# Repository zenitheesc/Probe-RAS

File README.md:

<h1 align="center" style="color:white; background-color:black">Probe-RAS</h1>
<h4 align="center"> Telecommunication board for the Zenith's Stack architecture.</h4>

<p align="center">

</p>

<p align="center">
    <a href="#environment-and-tools">Environment and Tools</a> •
    <a href="#Z-Hub">Z-Hub</a> •
    <a href="#Block-Diagram">Block Diagram</a> •
    <a href="#Schematic">Schematic</a> • 
    <a href="#Board">Board</a>
</p>

## Environment and tools

This board was designed using KiCad 5.1.10.

## Block Diagram

## Z-Hub

This board contains a Stack Connector, with the 2021 Z-Hub pinout.

<table align = "center">
  <thead>
    <tr>
      <th colspan=2>   Z-Hub 2021   </th>
    </tr>
  </thead>
  <tbody>
    <tr>
      <td>GND</td>
      <td>GND</td>
    </tr>
    <tr>
      <td>GND</td>
      <td>GND</td>
    </tr>
    <tr>
      <td>BAT+</td>
      <td>BAT+</td>
    </tr>
    <tr>
      <td>SOl+</td>
      <td>SOl-</td>
    </tr>
    <tr>
      <td>5V</td>
      <td>5V</td>
    </tr>
    <tr>
      <td>3V3</td>
      <td>3V3</td>
    </tr>
    <tr>
      <td>MISO1</td>
      <td>MOSI1</td>
    </tr>
    <tr>
      <td>SCK1</td>
      <td>CAN_H</td>
    </tr>
    <tr>
      <td>SDA </td>
      <td>CAN_L</td>
    </tr>
    <tr>
      <td>SCL</td>
      <td>CE02</td>
    </tr>
    <tr>
      <td>CE11</td>
      <td>CE12</td>
    </tr>
    <tr>
      <td>SDA1</td>
      <td>SCL1</td>
    </tr>
    <tr>
      <td>SDA2</td>
      <td>SCL2</td>
    </tr>
    <tr>
      <td>TX1</td>
      <td>RX1</td>
    </tr>
    <tr>
      <td>TX2</td>
      <td>RX2</td>
    </tr>
    <tr>
      <td>DIG1</td>
      <td>DIG6</td>
    </tr>
    <tr>
      <td>ALRT1</td>
      <td>/CHRG</td>
    </tr>
    <tr>
      <td>PWM</td>
      <td>DIG8</td>
    </tr>
    <tr>
      <td>/FAULT</td>
      <td>DIG9</td>
    </tr>
    <tr>
      <td>DIG5</td>
      <td>DIG10</td>
    </tr>
  </tbody>
</table>

## Schematic

The design was separated in hierarchical sheets to accommodate all components in an orderly way.

The first page contains the STM32L476 with all its accompanying circuits; crystals, debugging LED, Boot solder jumper, decoupling capacitors and reset button. On the same page you find the stack connector along with a programming and debugging connector, as well as the I2C pull-ups for all I2C lines. 

The second page contains the basic peripherals, such as the CAN transceiver, the 128 Mb flash memory and the SD card.

The last page contains all the sensors implemented on this board. The I2C ones are divided in two lines, the first one being I2CA, which covers the MS5607 Barometer, the HDC-1080 Humidity sensor and the ZMOD4410 CO2 and air quality sensor. The second I2C line is I2CB, focused on the attitude of the probe, covering the MPU-6050 Accelerometer and the MMC5983 Magnetometer.
This page also contains the Thermistor Interfaces, connected to the STM32 via SPI, but note that these components only use the MISO connection of the SPI line.
The last component that this page contains is the MPX5071GP, which outputs pressure data via a 5V line, read via an ADC by the STM32.

## Board

---

<p align="center">

</p>
<p align = "center">
<a href="zenith.eesc@gmail.com">zenith.eesc@gmail.com</a>
</p>

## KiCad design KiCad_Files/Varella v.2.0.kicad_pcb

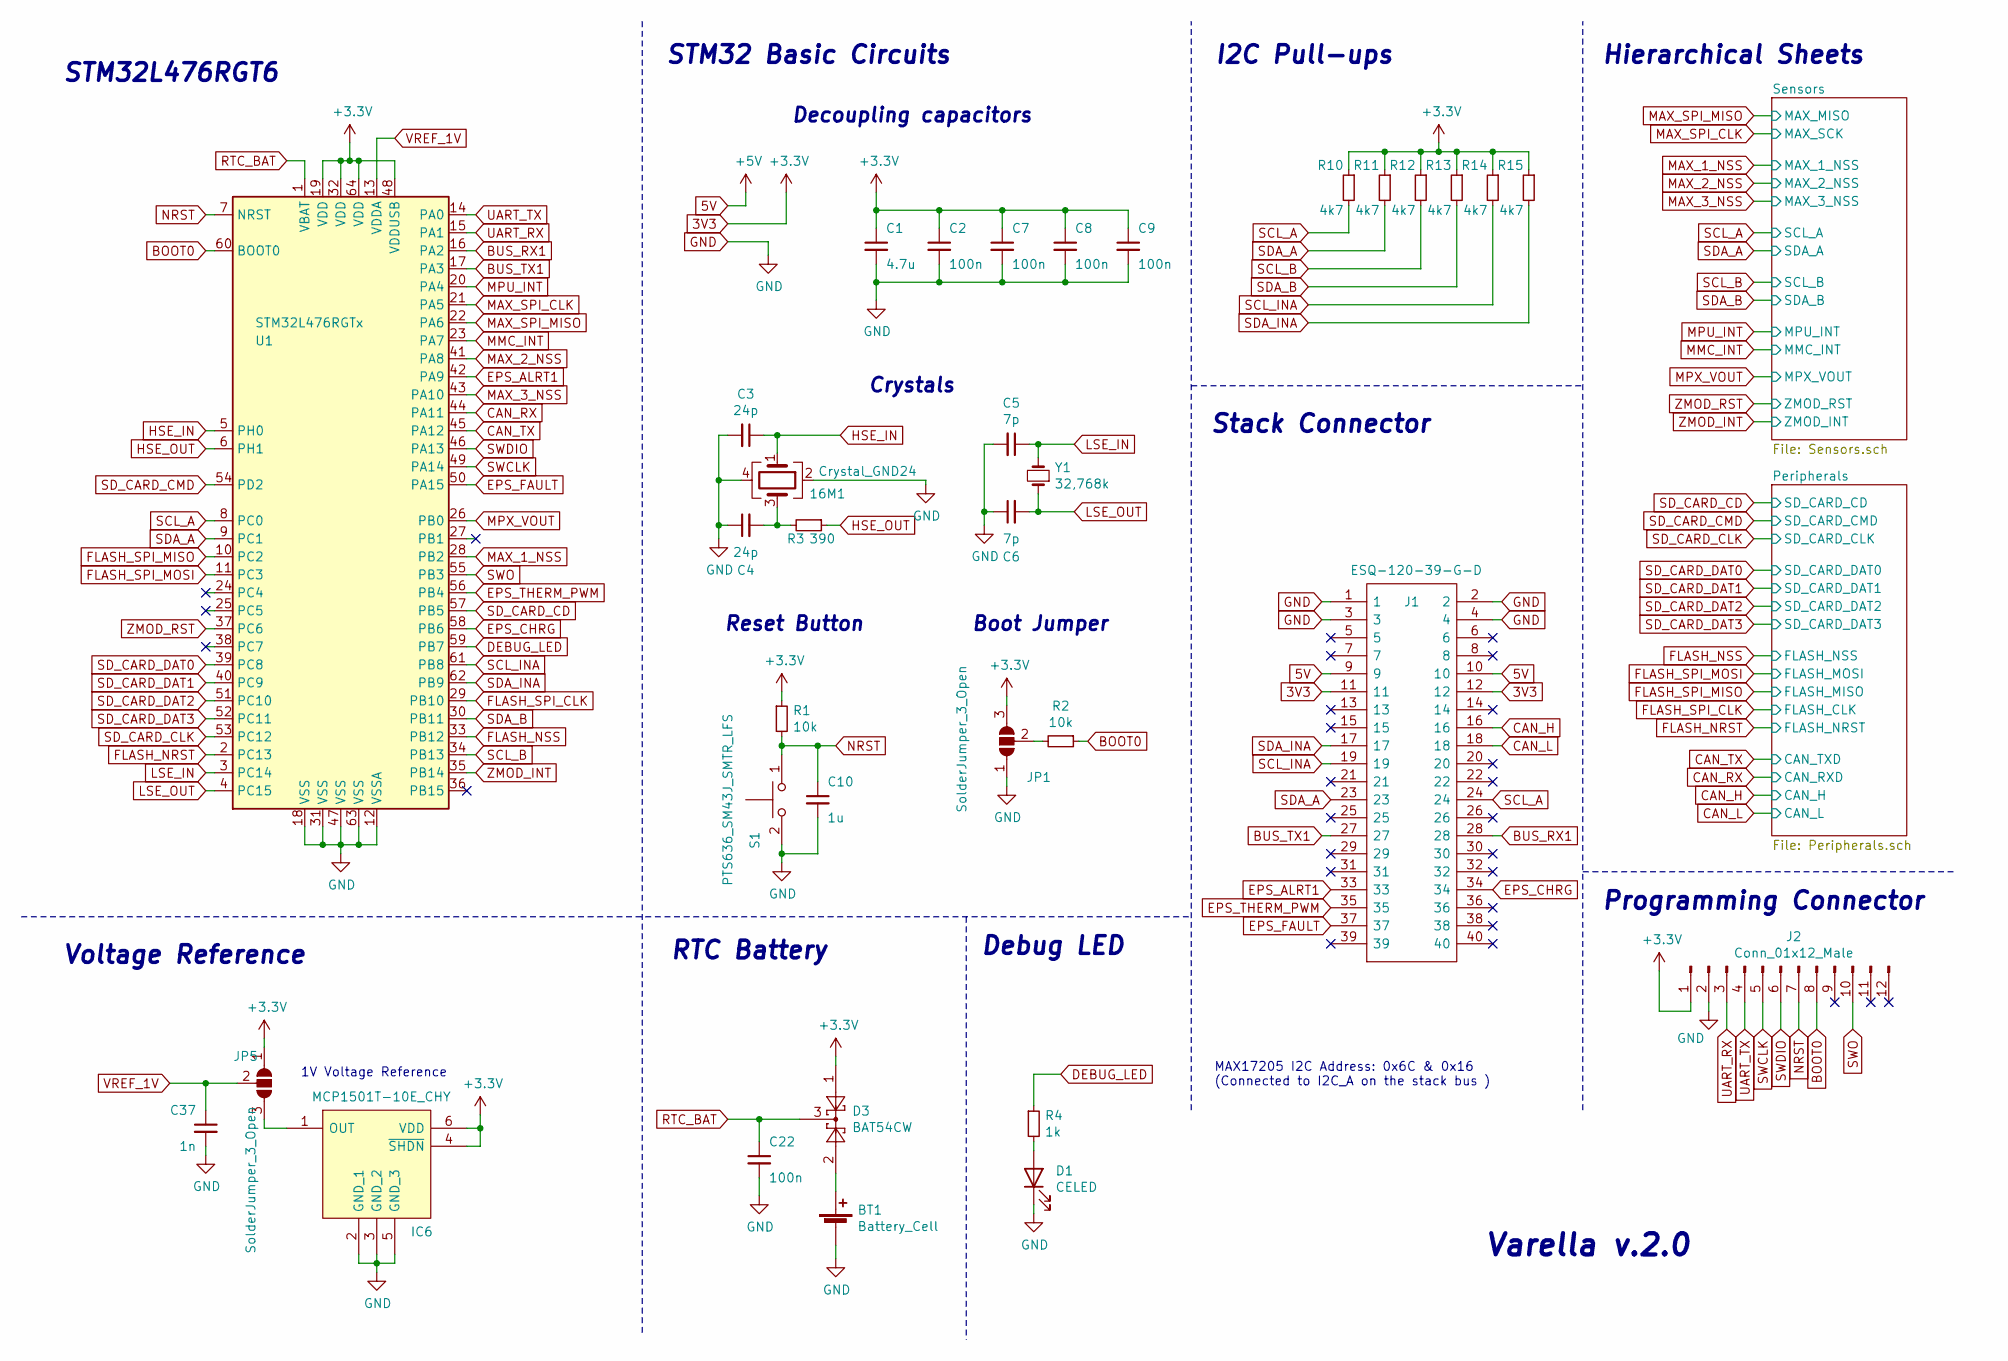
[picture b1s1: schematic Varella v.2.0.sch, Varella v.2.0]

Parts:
16M1: Crystal_GND24; Crystal_SMD_5032-4Pin_5.0x3.2mm_Hand_Soldering
BT1: Battery_Cell; 3030
C1: 4.7u; C_0805_2012Metric
C2, C7: 100n; C_0805_2012Metric
C3, C4: 24p; C_0805_2012Metric
C5, C6: 7p; C_0805_2012Metric
C8, C9, C22: 100n; C_0603_1608Metric
C10: 1u; C_0805_2012Metric
C37: 1n; C_0603_1608Metric
D1: CELED; LED_0805_2012Metric
D3: BAT54CW; SOT-323_SC-70
IC6: MCP1501T-10E_CHY; SOT95P280X145-6N; Mouser Part Number 579-MCP1501T-10E/CHY
J1: ESQ-120-39-G-D; ESQ-120-Y-X-D; Mouser Part Number 200-ESQ12039GD
J2: Conn_01x12_Male; 532611071
JP1, JP5: SolderJumper_3_Open; SolderJumper-3_P1.3mm_Open_RoundedPad1.0x1.5mm_NumberLabels
R1, R2: 10k; R_0805_2012Metric
R3: 390; R_0805_2012Metric
R4: 1k; R_0805_2012Metric
R10, R11, R12, R13, R14, R15: 4k7; R_0805_2012Metric
S1: PTS636_SM43J_SMTR_LFS; PTS636SM43JSMTRLFS; Mouser Part Number 611-PTS636SM43JSMTRL
U1: STM32L476RGTx; LQFP-64_10x10mm_P0.5mm
Y1: 32,768k; Crystal_SMD_3215-2Pin_3.2x1.5mm

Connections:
3V3: C1.1, C2.1, C7.1, C8.1, C9.1, D3.1, IC6.4 (~SHDN), IC6.6 (VDD), J1.11, J1.12, J2.1, JP1.3 (B), JP5.1 (A), R1.1, R10.1, R11.1, R12.1, R13.1, R14.1, R15.1, U1.19 (VDD), U1.32 (VDD), U1.48 (VDDUSB), U1.64 (VDD); also elsewhere on the board
5V: J1.9, J1.10; also elsewhere on the board
BOOT0: J2.8, R2.1, U1.60 (BOOT0)
BUS_RX1: J1.28, U1.16 (PA2)
BUS_TX1: J1.27, U1.17 (PA3)
CAN_H: J1.16; also elsewhere on the board
CAN_L: J1.18; also elsewhere on the board
CAN_RX: U1.44 (PA11); also elsewhere on the board
CAN_TX: U1.45 (PA12); also elsewhere on the board
DEBUG_LED: R4.1, U1.59 (PB7)
EPS_ALRT1: J1.33, U1.42 (PA9)
EPS_CHRG: J1.34, U1.58 (PB6)
EPS_FAULT: J1.37, U1.50 (PA15)
EPS_THERM_PWM: J1.35, U1.56 (PB4)
FLASH_NRST: U1.2 (PC13); also elsewhere on the board
FLASH_NSS: U1.33 (PB12); also elsewhere on the board
FLASH_SPI_CLK: U1.29 (PB10); also elsewhere on the board
FLASH_SPI_MISO: U1.10 (PC2); also elsewhere on the board
FLASH_SPI_MOSI: U1.11 (PC3); also elsewhere on the board
GND: 16M1.2, 16M1.4, BT1.2 (-), C1.2, C2.2, C3.2, C4.1, C5.2, C6.1, C7.2, C8.2, C9.2, C10.2, C22.2, C37.2, D1.1 (K), IC6.2 (GND_1), IC6.3 (GND_2), IC6.5 (GND_3), J1.1, J1.2, J1.3, J1.4, J2.2, JP1.1 (A), S1.2, U1.12 (VSSA), U1.18 (VSS), U1.31 (VSS), U1.47 (VSS), U1.63 (VSS); also elsewhere on the board
HSE_IN: 16M1.1, C3.1, U1.5 (PH0)
HSE_OUT: R3.1, U1.6 (PH1)
LSE_IN: C5.1, U1.3 (PC14), Y1.2
LSE_OUT: C6.2, U1.4 (PC15), Y1.1
MAX_1_NSS: U1.28 (PB2); also elsewhere on the board
MAX_2_NSS: U1.41 (PA8); also elsewhere on the board
MAX_3_NSS: U1.43 (PA10); also elsewhere on the board
MAX_SPI_CLK: U1.21 (PA5); also elsewhere on the board
MAX_SPI_MISO: U1.22 (PA6); also elsewhere on the board
MMC_INT: U1.23 (PA7); also elsewhere on the board
MPU_INT: U1.20 (PA4); also elsewhere on the board
MPX_VOUT: U1.26 (PB0); also elsewhere on the board
NRST: C10.1, J2.7, R1.2, S1.1, U1.7 (NRST)
unnamed: 16M1.3, C4.2, R3.2
unnamed: BT1.1 (+), D3.2
unnamed: D1.2 (A), R4.2
unnamed: IC6.1 (OUT), JP5.3 (B)
unnamed: JP1.2 (C), R2.2
RTC_BAT: C22.1, D3.3, U1.1 (VBAT)
SCL_A: J1.24, R10.2, U1.8 (PC0); also elsewhere on the board
SCL_B: R12.2, U1.34 (PB13); also elsewhere on the board
SCL_INA: J1.19, R14.2, U1.61 (PB8)
SDA_A: J1.23, R11.2, U1.9 (PC1); also elsewhere on the board
SDA_B: R13.2, U1.30 (PB11); also elsewhere on the board
SDA_INA: J1.17, R15.2, U1.62 (PB9)
SD_CARD_CD: U1.57 (PB5); also elsewhere on the board
SD_CARD_CLK: U1.53 (PC12); also elsewhere on the board
SD_CARD_CMD: U1.54 (PD2); also elsewhere on the board
SD_CARD_DAT0: U1.39 (PC8); also elsewhere on the board
SD_CARD_DAT1: U1.40 (PC9); also elsewhere on the board
SD_CARD_DAT2: U1.51 (PC10); also elsewhere on the board
SD_CARD_DAT3: U1.52 (PC11); also elsewhere on the board
SWCLK: J2.5, U1.49 (PA14)
SWDIO: J2.6, U1.46 (PA13)
SWO: J2.10, U1.55 (PB3)
UART_RX: J2.3, U1.15 (PA1)
UART_TX: J2.4, U1.14 (PA0)
VREF_1V: C37.1, JP5.2 (C), U1.13 (VDDA)
ZMOD_INT: U1.35 (PB14); also elsewhere on the board
ZMOD_RST: U1.37 (PC6); also elsewhere on the board

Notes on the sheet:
Programming Connector
Stack Connector
Hierarchical Sheets
Varella v.2.0
STM32L476RGT6
I2C Pull-ups
MAX17205 I2C Address: 0x6C & 0x16 (Connected to I2C_A on the stack bus )
1V Voltage Reference
Voltage Reference
RTC Battery
Debug LED
STM32 Basic Circuits
Crystals
Decoupling capacitors
Reset Button
Boot Jumper

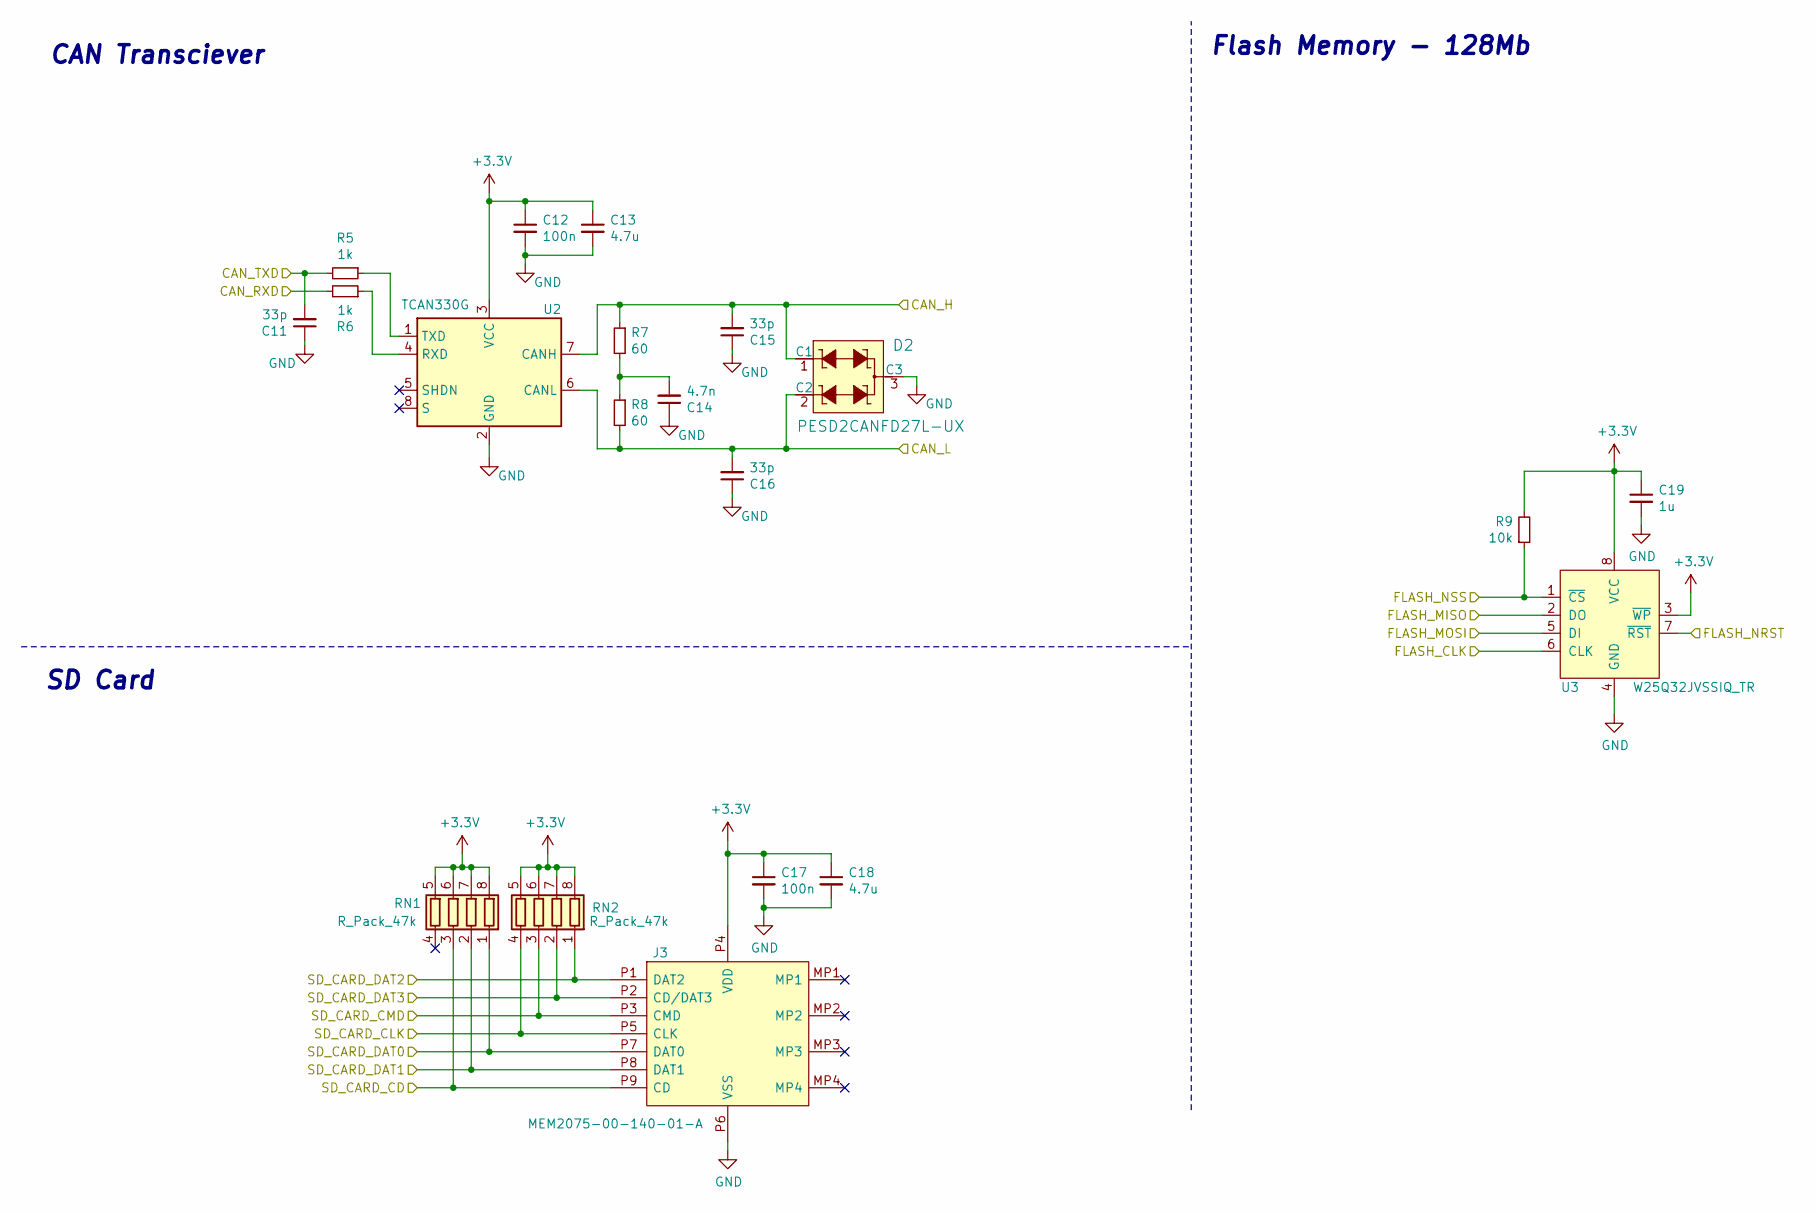
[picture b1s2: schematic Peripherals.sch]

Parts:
C11, C15, C16: 33p; C_0805_2012Metric
C12, C17: 100n; C_0805_2012Metric
C13, C18: 4.7u; C_0805_2012Metric
C14: 4.7n; C_0805_2012Metric
C19: 1u; C_0805_2012Metric
D2: PESD2CANFD27L-UX; SOT-23-3; MPN PESD2CAN,215; Digi-Key_PN 1727-3891-1-ND
J3: MEM2075-00-140-01-A; MEM20750014001A; Mouser Part Number 640-MEM20750014001A
R5, R6: 1k; R_0805_2012Metric
R7, R8: 60; R_0805_2012Metric
R9: 10k; R_0805_2012Metric
RN1, RN2: R_Pack_47k; YC164JR07220RL
U2: TCAN330G; SOIC-8_3.9x4.9mm_P1.27mm
U3: W25Q32JVSSIQ_TR; SOIC-8_W5.6mm; MPN W25Q32JVSSIQ TR; Digi-Key_PN W25Q32JVSSIQCT-ND

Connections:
3V3: C12.1, C13.1, C17.1, C18.1, C19.1, J3.P4 (VDD), R9.2, RN1.5 (R4.2), RN1.6 (R3.2), RN1.7 (R2.2), RN1.8 (R1.2), RN2.5 (R4.2), RN2.6 (R3.2), RN2.7 (R2.2), RN2.8 (R1.2), U2.3 (VCC), U3.3 (~WP), U3.8 (VCC); also elsewhere on the board
CAN_H: C15.2, D2.1 (C1), R7.1, U2.7 (CANH); also elsewhere on the board
CAN_L: C16.2, D2.2 (C2), R8.2, U2.6 (CANL); also elsewhere on the board
CAN_RX: R6.2; also elsewhere on the board
CAN_TX: C11.2, R5.2; also elsewhere on the board
FLASH_NRST: U3.7 (~RST); also elsewhere on the board
FLASH_NSS: R9.1, U3.1 (~CS); also elsewhere on the board
FLASH_SPI_CLK: U3.6 (CLK); also elsewhere on the board
FLASH_SPI_MISO: U3.2 (DO); also elsewhere on the board
FLASH_SPI_MOSI: U3.5 (DI); also elsewhere on the board
GND: C11.1, C12.2, C13.2, C14.1, C15.1, C16.1, C17.2, C18.2, C19.2, D2.3 (C3), J3.P6 (VSS), U2.2 (GND), U3.4 (GND); also elsewhere on the board
unnamed: C14.2, R7.2, R8.1
unnamed: R5.1, U2.1 (TXD)
unnamed: R6.1, U2.4 (RXD)
SD_CARD_CD: J3.P9 (CD), RN1.3 (R3.1); also elsewhere on the board
SD_CARD_CLK: J3.P5 (CLK), RN2.4 (R4.1); also elsewhere on the board
SD_CARD_CMD: J3.P3 (CMD), RN2.3 (R3.1); also elsewhere on the board
SD_CARD_DAT0: J3.P7 (DAT0), RN1.1 (R1.1); also elsewhere on the board
SD_CARD_DAT1: J3.P8 (DAT1), RN1.2 (R2.1); also elsewhere on the board
SD_CARD_DAT2: J3.P1 (DAT2), RN2.1 (R1.1); also elsewhere on the board
SD_CARD_DAT3: J3.P2 (CD/DAT3), RN2.2 (R2.1); also elsewhere on the board

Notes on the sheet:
CAN Transciever
SD Card
Flash Memory - 128Mb

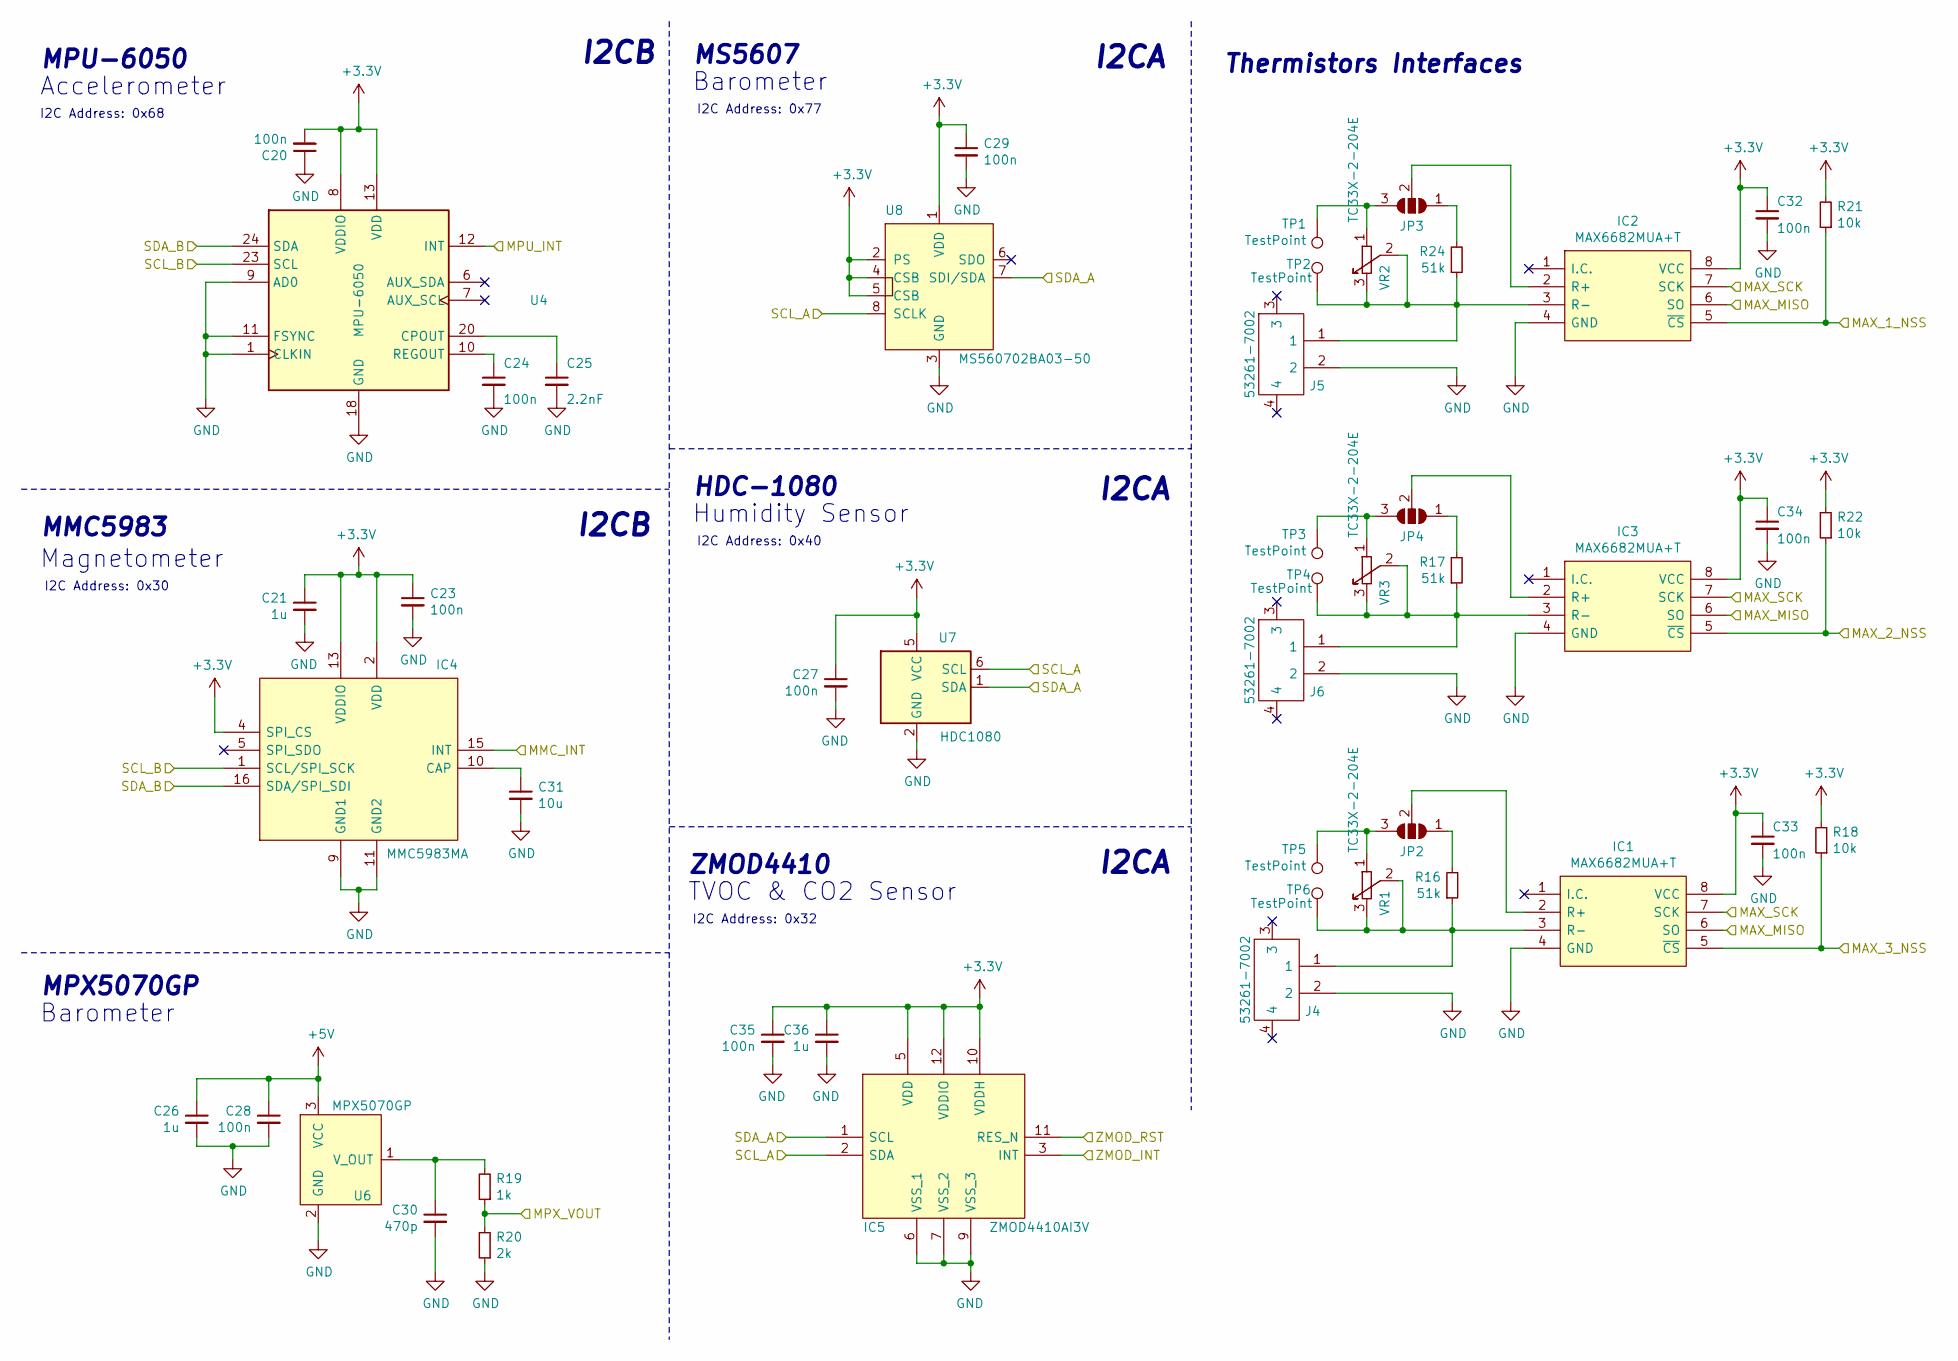
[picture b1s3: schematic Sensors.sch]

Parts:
C20, C23, C24, C27, C28, C29, C32, C33, C34, C35: 100n; C_0805_2012Metric
C21, C26, C36: 1u; C_0805_2012Metric
C25: 2.2nF; C_0805_2012Metric
C30: 470p; C_0805_2012Metric
C31: 10u; C_0805_2012Metric
IC1, IC2, IC3: MAX6682MUA+T; SOP65P490X110-8N; Mouser Part Number 700-MAX6682MUAT
IC4: MMC5983MA; Mouser Part Number 438-MMC5983MA
IC5: ZMOD4410AI3V; Mouser Part Number 972-ZMOD4410AI3V
J4, J5, J6: 53261-7002; 532617002; Mouser Part Number 538-53261-7002
JP2, JP3, JP4: SolderJumper_3_Open; SolderJumper-3_P1.3mm_Open_RoundedPad1.0x1.5mm_NumberLabels
R16, R17, R24: 51k; R_0805_2012Metric
R18, R21, R22: 10k; R_0805_2012Metric
R19: 1k; R_0805_2012Metric
R20: 2k; R_0805_2012Metric
TP1, TP2, TP3, TP4, TP5, TP6: TestPoint; TestPoint_Pad_D2.0mm
U4: MPU-6050; InvenSense_QFN-24_4x4mm_P0.5mm
U6: MPX5070GP
U7: HDC1080; Texas_PWSON-N6
U8: MS560702BA03-50; SMD-8_5x3mm; MPN MS560702BA03-50; Digi-Key_PN 223-1198-1-ND
VR1, VR2, VR3: TC33X-2-204E; TC33X-2_1; Mouser Part Number 652-TC33X-2-204E

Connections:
3V3: C20.2, C21.1, C23.1, C27.1, C29.1, C32.1, C33.1, C34.1, C35.1, C36.1, IC1.8 (VCC), IC2.8 (VCC), IC3.8 (VCC), IC4.2 (VDD), IC4.4 (SPI_CS), IC4.13 (VDDIO), IC5.5 (VDD), IC5.10 (VDDH), IC5.12 (VDDIO), R18.2, R21.2, R22.2, U4.8 (VDDIO), U4.13 (VDD), U7.5 (VCC), U8.1 (VDD), U8.2 (PS), U8.4 (CSB), U8.5 (CSB); also elsewhere on the board
5V: C26.1, C28.1, U6.3 (VCC); also elsewhere on the board
GND: C20.1, C21.2, C23.2, C24.2, C25.2, C26.2, C27.2, C28.2, C29.2, C30.2, C31.2, C32.2, C33.2, C34.2, C35.2, C36.2, IC1.4 (GND), IC2.4 (GND), IC3.4 (GND), IC4.9 (GND1), IC4.11 (GND2), IC5.6 (VSS_1), IC5.7 (VSS_2), IC5.9 (VSS_3), J4.2, J5.2, J6.2, R20.1, U4.1 (CLKIN), U4.9 (AD0), U4.11 (FSYNC), U4.18 (GND), U6.2 (GND), U7.2 (GND), U8.3 (GND); also elsewhere on the board
MAX_1_NSS: IC2.5 (~CS), R21.1; also elsewhere on the board
MAX_2_NSS: IC3.5 (~CS), R22.1; also elsewhere on the board
MAX_3_NSS: IC1.5 (~CS), R18.1; also elsewhere on the board
MAX_SPI_CLK: IC1.7 (SCK), IC2.7 (SCK), IC3.7 (SCK); also elsewhere on the board
MAX_SPI_MISO: IC1.6 (SO), IC2.6 (SO), IC3.6 (SO); also elsewhere on the board
MMC_INT: IC4.15 (INT); also elsewhere on the board
MPU_INT: U4.12 (INT); also elsewhere on the board
MPX_VOUT: R19.1, R20.2; also elsewhere on the board
unnamed: C24.1, U4.10 (REGOUT)
unnamed: C25.1, U4.20 (CPOUT)
unnamed: C30.1, R19.2, U6.1 (V_OUT)
unnamed: C31.1, IC4.10 (CAP)
unnamed: IC1.2 (R+), JP2.2 (C)
unnamed: IC1.3 (R-), J4.1, R16.1, TP6.1, VR1.2, VR1.3
unnamed: IC2.2 (R+), JP3.2 (C)
unnamed: IC2.3 (R-), J5.1, R24.1, TP2.1, VR2.2, VR2.3
unnamed: IC3.2 (R+), JP4.2 (C)
unnamed: IC3.3 (R-), J6.1, R17.1, TP4.1, VR3.2, VR3.3
unnamed: JP2.1 (A), R16.2
unnamed: JP2.3 (B), TP5.1, VR1.1
unnamed: JP3.1 (A), R24.2
unnamed: JP3.3 (B), TP1.1, VR2.1
unnamed: JP4.1 (A), R17.2
unnamed: JP4.3 (B), TP3.1, VR3.1
SCL_A: IC5.2 (SDA), U7.6 (SCL), U8.8 (SCLK); also elsewhere on the board
SCL_B: IC4.1 (SCL/SPI_SCK), U4.23 (SCL); also elsewhere on the board
SDA_A: IC5.1 (SCL), U7.1 (SDA), U8.7 (SDI/SDA); also elsewhere on the board
SDA_B: IC4.16 (SDA/SPI_SDI), U4.24 (SDA); also elsewhere on the board
ZMOD_INT: IC5.3 (INT); also elsewhere on the board
ZMOD_RST: IC5.11 (RES_N); also elsewhere on the board

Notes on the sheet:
Thermistors Interfaces
MPU-6050
MS5607
MMC5983
HDC-1080
Humidity Sensor
Magnetometer
Accelerometer
Barometer
MPX5070GP
I2C Address: 0x77
I2C Address: 0x40
I2C Address: 0x68
I2C Address: 0x30
ZMOD4410
TVOC & CO2 Sensor
I2C Address: 0x32
I2CA
I2CB

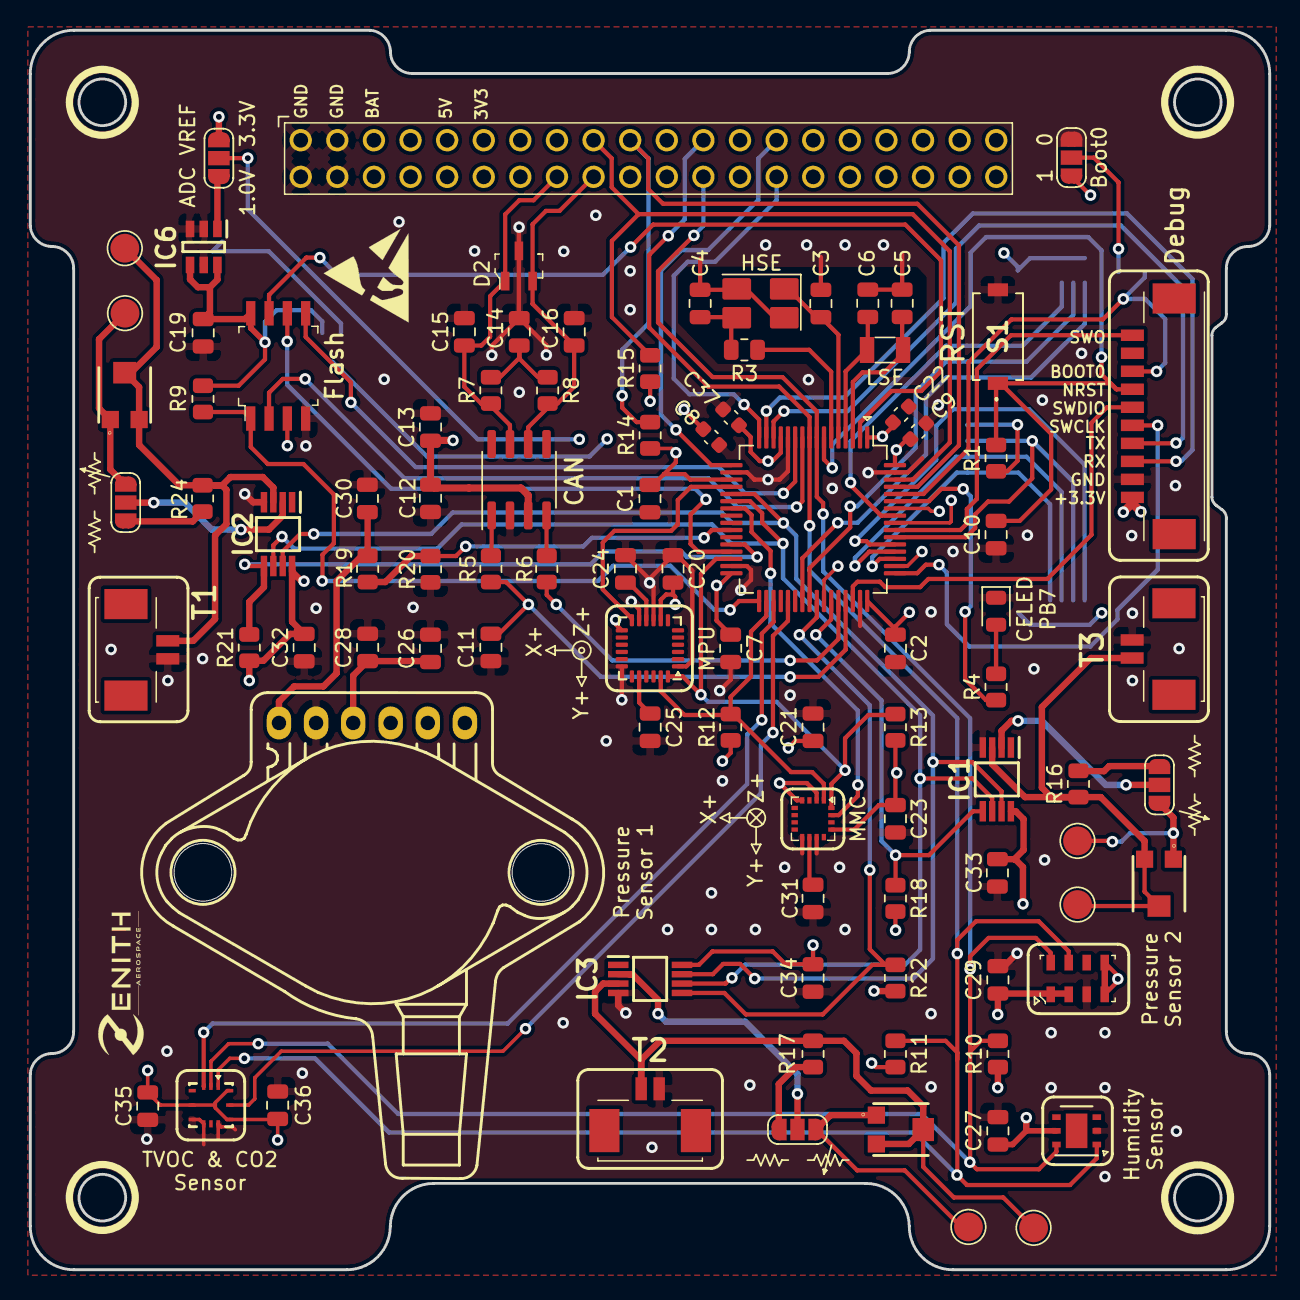
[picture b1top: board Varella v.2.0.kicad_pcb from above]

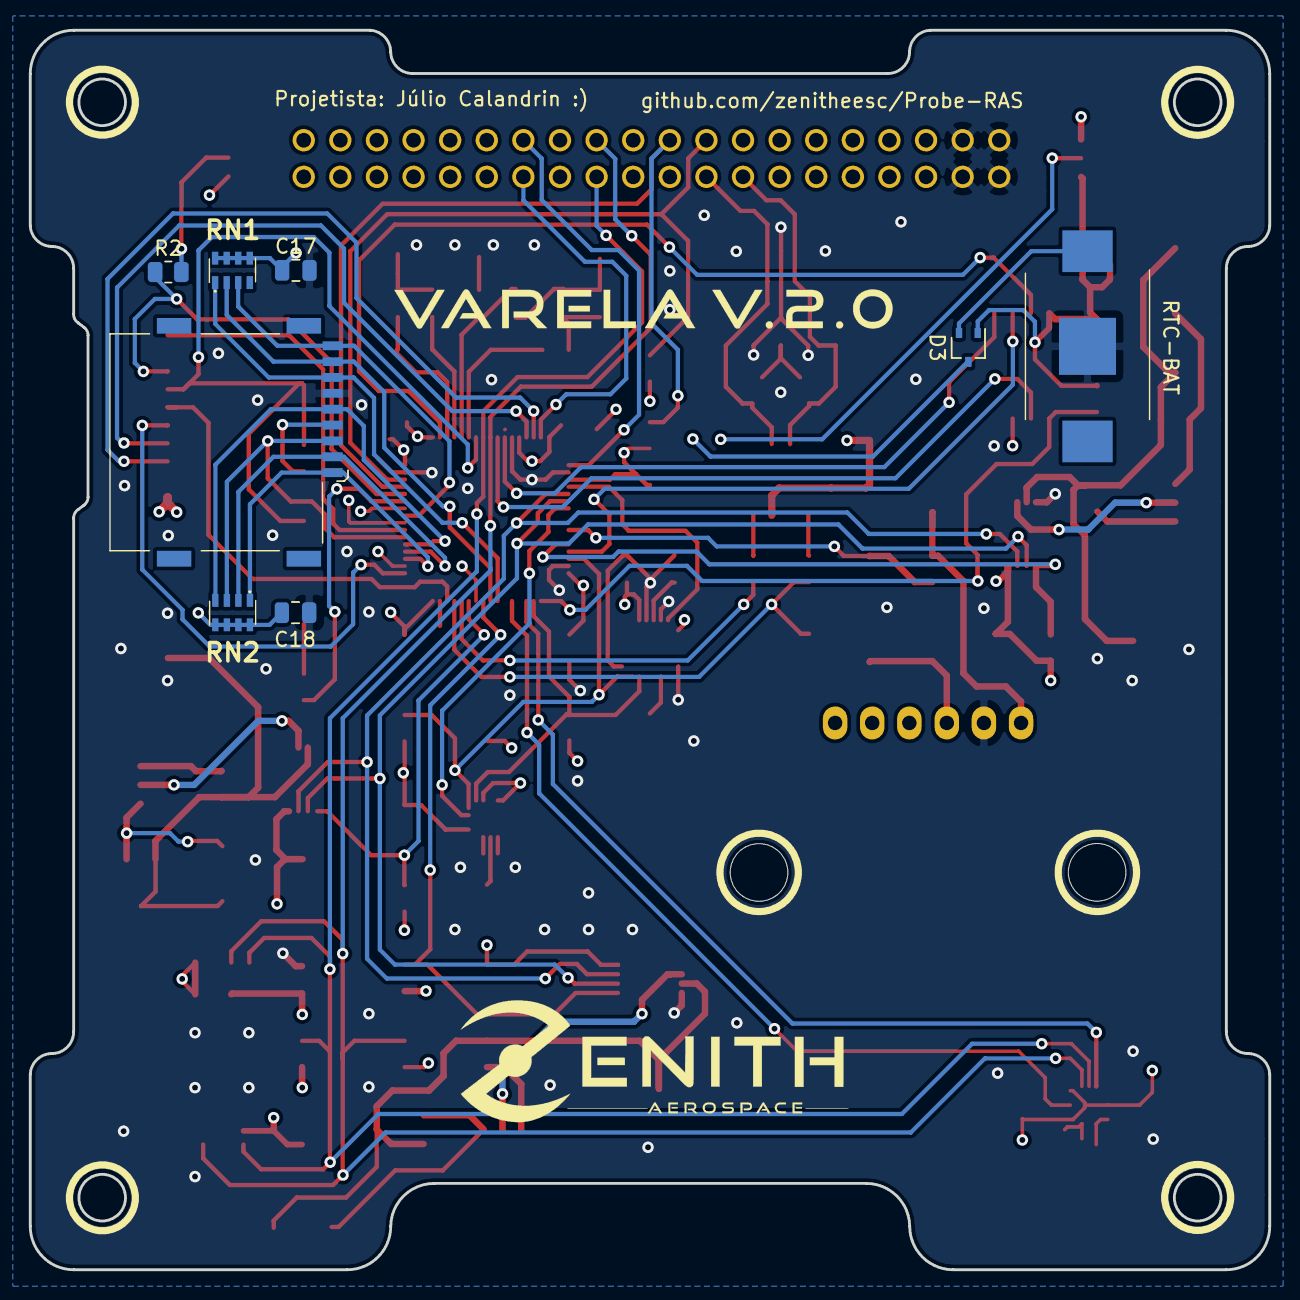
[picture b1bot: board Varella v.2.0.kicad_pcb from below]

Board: 4 copper layers, 86.0 x 86.0 mm, 102 parts (8 on the bottom side), 79 nets.

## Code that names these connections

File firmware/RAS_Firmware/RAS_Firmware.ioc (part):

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Mcu.Name=STM32L476R(C-E-G)Tx
Mcu.Package=LQFP64
Mcu.UserName=STM32L476RGTx
PA10.Mode=Asynchronous
PA10.Signal=USART1_RX
PA11.Mode=CAN_Activate
PA11.Signal=CAN1_RX
PA12.Mode=CAN_Activate
PA12.Signal=CAN1_TX
PA13\ (JTMS-SWDIO).Mode=Serial_Wire
PA13\ (JTMS-SWDIO).Signal=SYS_JTMS-SWDIO
PA14\ (JTCK-SWCLK).Mode=Serial_Wire
PA14\ (JTCK-SWCLK).Signal=SYS_JTCK-SWCLK
PA5.Mode=Full_Duplex_Master
PA5.Signal=SPI1_SCK
PA6.Mode=Full_Duplex_Master
PA6.Signal=SPI1_MISO
PA7.Mode=Full_Duplex_Master
PA7.Signal=SPI1_MOSI
PA9.Mode=Asynchronous
PA9.Signal=USART1_TX
PB5.Signal=GPIO_Input
PB6.Mode=I2C
PB6.Signal=I2C1_SCL
PB7.Mode=I2C
PB7.Signal=I2C1_SDA
PC10.Mode=SD_4_bits_Wide_bus
PC10.Signal=SDMMC1_D2
PC11.Mode=SD_4_bits_Wide_bus
PC11.Signal=SDMMC1_D3
PC12.Mode=SD_4_bits_Wide_bus
PC12.Signal=SDMMC1_CK
PC14-OSC32_IN\ (PC14).Mode=LSE-External-Oscillator
PC14-OSC32_IN\ (PC14).Signal=RCC_OSC32_IN
PC15-OSC32_OUT\ (PC15).Mode=LSE-External-Oscillator
PC15-OSC32_OUT\ (PC15).Signal=RCC_OSC32_OUT
PC8.Mode=SD_4_bits_Wide_bus
PC8.Signal=SDMMC1_D0
PC9.Mode=SD_4_bits_Wide_bus
PC9.Signal=SDMMC1_D1
PD2.Mode=SD_4_bits_Wide_bus
PD2.Signal=SDMMC1_CMD
PH0-OSC_IN\ (PH0).Mode=HSE-External-Oscillator
PH0-OSC_IN\ (PH0).Signal=RCC_OSC_IN
PH1-OSC_OUT\ (PH1).Mode=HSE-External-Oscillator
PH1-OSC_OUT\ (PH1).Signal=RCC_OSC_OUT
RCC.HSE_VALUE=8000000
RCC.SYSCLKFreq_VALUE=80000000
RCC.SYSCLKSource=RCC_SYSCLKSOURCE_PLLCLK
board=custom

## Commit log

2022-01-19 Add Board
2022-01-19 Add Block Diagram
2022-01-20 Add shapes3D folder
    Now all 3D models for the components are stored in a single folder, thanks to the Archive Plugin from https://github.com/MitjaNemec/Kicad_action_plugins.git
2022-01-20 Revert "Add shapes3D folder"
    This reverts commit 1c3042b7a1c052b8553a455bf3bd885d3494e48a.
2022-01-20 Add shapes3D folder again
    Something went wrong on the last commit. The hierarchical sheets had been corrupted after the archiving process, so I reverted the commit and did the procedure again. Everything appears to be working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
2022-01-20 Revert "Delete archive_project.log"
    This reverts commit 61f9e4587e3aeb6e86bf636a17929865b062fe7a.
2022-01-20 Revert "Add shapes3D folder again"
    This reverts commit 7987a310af828f940c17547aa6162ac2ebe2b018.
2022-01-20 Archive project
2022-01-20 Update Archive
2022-01-20 Archive Schematic
2022-01-26 README: Delete duplicated header
2022-01-27 Add Traces to Stack Connector
    Connects the Interrupts and PWM pins that come from the EPS boards through the Stack Connector to Varella's STM32.
2022-01-27 Add BOM and update image of the first page
2022-01-28 Gerado projeto da CubeIDE
2022-02-03 Correct diagram component name
    MAX6682 replaced the MAX31856 during development, but the diagram was never updated.
2022-02-05 Update RTC Battery Silk Screen name
2022-02-09 Add 1,024 V voltage reference for the ADC.
    We realised that the MPX5700 barometer would only output a voltage from 0 to 0,66 V in the altitude range of the radiosonde trajectory. By adding this voltage reference to the ADC we will have much b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
2022-03-01 Added missing .cproject, but should it be here?
2022-03-01 Added ioc with correct FreeRTOS config for code generation
2022-03-01 Added architecture files for testing
2022-06-09 Reroutes voltage reference selector trace for better aesthetics.
2022-07-14 Change silkscreen
    Adds the name "Varela" to the board.
    Also adds the name of the designer (me).
